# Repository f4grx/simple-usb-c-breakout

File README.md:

usb-c breakout
==============
Simple USB-C breakout to access USB-2 bus lines of a USB-C Connector.

Footprints are provided to add resistors on the CC lines to configure either as source or sink. Soldering wires on the resistor pads access the CC1 and CC2 lines.

Could be used for USB PD experiments.

PCB were done at oshpark by uploading the kicad_pcb directly, that's why there are no gerbers.

The project does not depend on ANY external kicad lib. All required footprints and symbols are available in this repo in a local library.

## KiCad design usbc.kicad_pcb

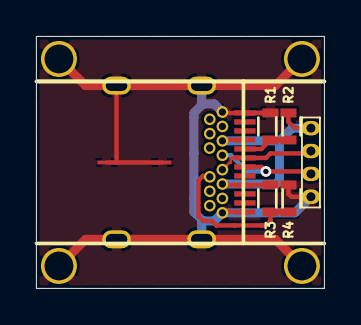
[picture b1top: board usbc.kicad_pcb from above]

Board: 2 copper layers, 16.0 x 14.0 mm, 10 parts (0 on the bottom side), 6 nets.

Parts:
J1, J2, J3, J4: PIN; HOLE_1.6mm
P1: CONN_01X04; PINS-1.27-1x4
R1, R2, R3, R4: RSMALL; 0603_m1608
USB1: Wurth-632723300011

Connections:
/CC1: R1.2, R2.1, USB1.5
/CC2: R3.2, R4.1, USB1.17
/DN: P1.2, USB1.7, USB1.19
/DP: P1.3, USB1.6, USB1.18
/GND: J1.1, J2.1, J3.1, J4.1, P1.1, R2.2, R4.2, USB1.1, USB1.12, USB1.13, USB1.24, USB1.26, USB1.27
/VBUS: P1.4, R1.1, R3.1, USB1.4, USB1.9, USB1.16, USB1.21

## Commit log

2020-10-22 initial state
